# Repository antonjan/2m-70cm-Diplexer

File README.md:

# 2m-70cm-Diplexer
This project will have the VHF  UHF Diplexer

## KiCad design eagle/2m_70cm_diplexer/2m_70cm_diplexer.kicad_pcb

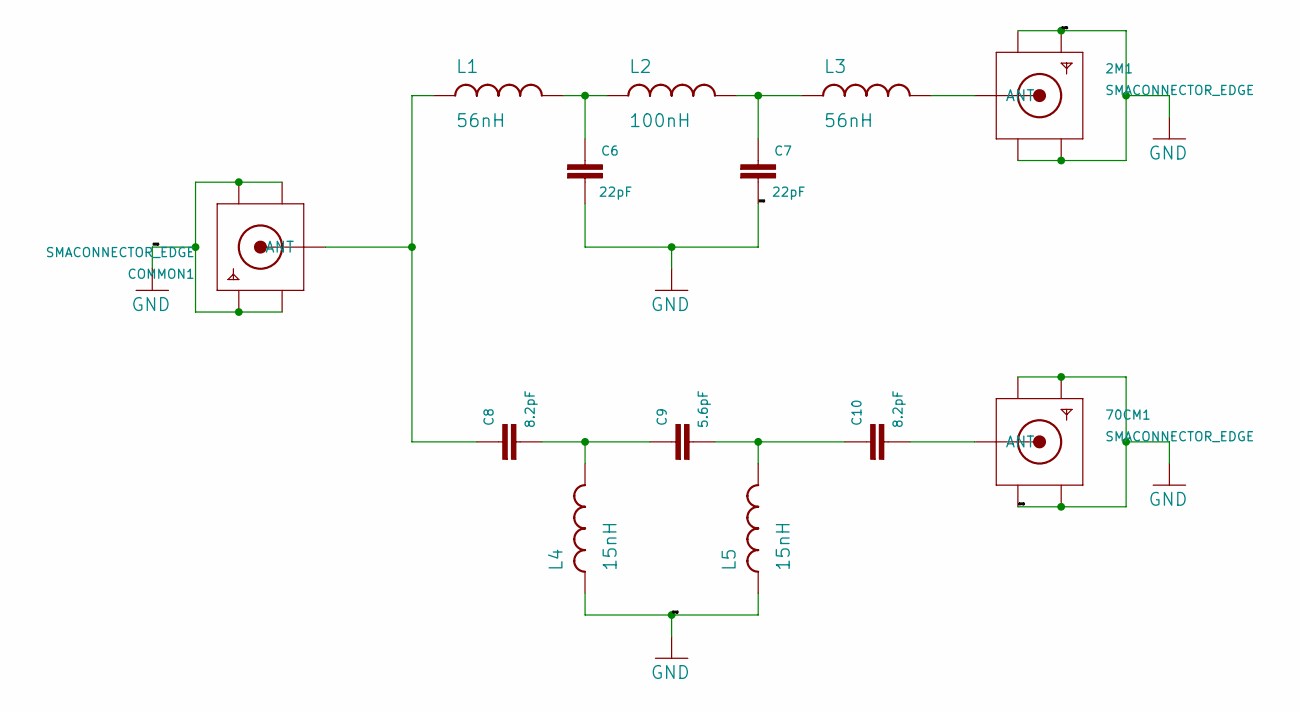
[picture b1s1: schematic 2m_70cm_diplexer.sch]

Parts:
2M1, 70CM1: SMACONNECTOR_EDGE; SMA_EDGELAUNCH
C6, C7: 22pF; 0805
C8, C10: 8.2pF; 0805
C9: 5.6pF; 0805
COMMON1: SMACONNECTOR_EDGE; SMA_EDGELAUNCH
L1, L3: 56nH; 1008INDUCTOR
L2: 100nH; 1008INDUCTOR
L4, L5: 15nH; 1008INDUCTOR

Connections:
GND: 2M1.GND@1 (GND4), 2M1.GND@2 (GND3), 2M1.GND@3 (GND2), 2M1.GND@4 (GND1), 70CM1.GND@1 (GND4), 70CM1.GND@2 (GND3), 70CM1.GND@3 (GND2), 70CM1.GND@4 (GND1), C6.P$1, C7.P$1, COMMON1.GND@1 (GND4), COMMON1.GND@2 (GND3), COMMON1.GND@3 (GND2), COMMON1.GND@4 (GND1), L4.P$1, L5.P$1
unnamed: 2M1.P (ANT), L3.P$2
unnamed: 70CM1.P (ANT), C10.P$1
unnamed: C6.P$2, L1.P$2, L2.P$1
unnamed: C7.P$2, L2.P$2, L3.P$1
unnamed: C8.P$1, C9.P$2, L4.P$2
unnamed: C8.P$2, COMMON1.P (ANT), L1.P$1
unnamed: C9.P$1, C10.P$2, L5.P$2

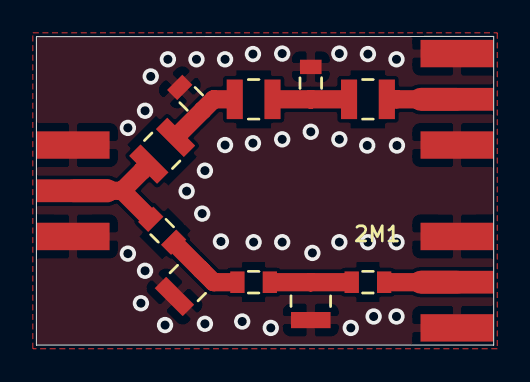
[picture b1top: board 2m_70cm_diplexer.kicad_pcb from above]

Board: 2 copper layers, 25.4 x 17.1 mm, 13 parts (0 on the bottom side), 8 nets.

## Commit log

2020-03-20 adding kicad vertion from eagle
